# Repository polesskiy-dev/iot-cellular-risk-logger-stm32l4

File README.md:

# IoT Cellular Risk Data Logger
## Based on Cortex M4 STM32L4 and cellular Simcom SIM7070

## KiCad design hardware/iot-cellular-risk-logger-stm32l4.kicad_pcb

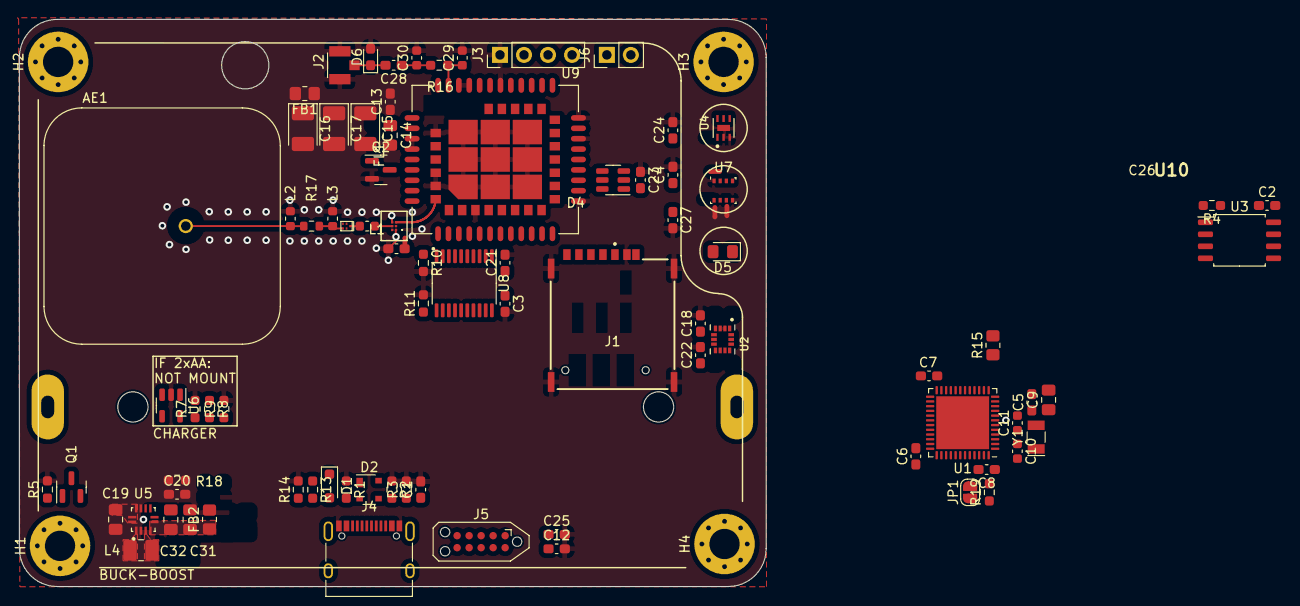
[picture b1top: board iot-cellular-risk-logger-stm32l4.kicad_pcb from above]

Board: 4 copper layers, 79.0 x 60.0 mm, 91 parts (1 on the bottom side), 73 nets.

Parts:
AE1: GNSS Antenna; XDCR_APAE1590R2540AKDB1-T
BT1: 18650 Li-Ion; BAT_BH-18650-PC
C1: 4n7; C_0603_1608Metric_Pad1.08x0.95mm_HandSolder
C2, C3, C4, C5, C6, C7, C8, C12, C13, C18, C21, C22, C23, C24, C25, C26, C27: 100n; C_0603_1608Metric_Pad1.08x0.95mm_HandSolder
C9, C19, C31, C32: 10u; C_0805_2012Metric_Pad1.18x1.45mm_HandSolder
C10, C11: 22p; C_0603_1608Metric
C14: 1u; C_0805_2012Metric_Pad1.18x1.45mm_HandSolder
C15, C16, C17: 100uF; CP_EIA-3528-15_AVX-H_Pad1.50x2.35mm_HandSolder
C20: 1n; C_0603_1608Metric_Pad1.08x0.95mm_HandSolder
C28: 100p; C_0603_1608Metric_Pad1.08x0.95mm_HandSolder
C29, C30: 0p; C_0603_1608Metric
D1: BAT60A; D_SOD-323_HandSoldering
D2: PRTR5V0U2X; SOT-143
D4: SMF05CT1G; SOT-23-6
D5: LED; LED_0805_2012Metric_Pad1.15x1.40mm_HandSolder
D6: TVS 5V; D_0603_1608Metric_Pad1.05x0.95mm_HandSolder
FB1, FB2: 330; R_0805_2012Metric_Pad1.20x1.40mm_HandSolder
FL1: SAFFB1G56KB0F0A; Filter_1109-5_1.1x0.9mm
H1, H2, H3, H4: MountingHole_Pad; MountingHole_3.2mm_M3_Pad_Via
J1: Nano SIM; GCT_SIM8066-6-1-14-01-A_REVA
J2: U.FL Antenna Connector (Male); HRS_U.FL-R-SMT_01_
J3: GSM_USB; PinHeader_1x04_P2.54mm_Vertical
J4: USB Type-C; USB_C_Receptacle_XKB_U262-16XN-4BVC11
J5: TagConnect SWD ARM; Tag-Connect_TC2050-IDC-NL_2x05_P1.27mm_Vertical_with_bottom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
J6: GSM_DEBUG_UART; PinHeader_1x02_P2.54mm_Vertical
JP1: SolderJumper_2_Open; SolderJumper-2_P1.3mm_Open_RoundedPad1.0x1.5mm
L1: 8.2nH; L_0603_1608Metric
L2, L3: 0L; L_0603_1608Metric
L4: 1.5uH; L_1008_2520Metric_Pad1.43x2.20mm_HandSolder
NT1, NT2, NT3, NT6: NetTie_2; NetTie-2_SMD_Pad0.5mm
Q1: IRLML6401; SOT-23
Q2: DTC143Z; SOT-23
R1, R2: 5k1; R_0603_1608Metric_Pad0.98x0.95mm_HandSolder
R3, R18: 1M; R_0603_1608Metric_Pad0.98x0.95mm_HandSolder
R4, R19: 10k; R_0603_1608Metric_Pad0.98x0.95mm_HandSolder
R5, R9, R10, R11, R13, R14: 47k; R_0603_1608Metric_Pad0.98x0.95mm_HandSolder
R7: 2k5; R_0603_1608Metric_Pad0.98x0.95mm_HandSolder
R8: 100k; R_0603_1608Metric_Pad0.98x0.95mm_HandSolder
R15: 1k; R_0805_2012Metric_Pad1.20x1.40mm_HandSolder
R16: 0R; R_0603_1608Metric_Pad0.98x0.95mm_HandSolder
R17: 0R; R_0603_1608Metric
U1: STM32L433CBUx; QFN-48-1EP_7x7mm_P0.5mm_EP5.6x5.6mm
U2: LSM6DSO; PQFN50P250X300X86-14N
U3: W25Q64JV; SOIC-8_5.23x5.23mm_P1.27mm
U4: OPT3001DNPR; SON65P200X200X65-7N
U5: TPS63051; QFN50P250X250X100-12N
U6: MCP73831-2-OT; SOT-23-5
U7: BME280; Bosch_LGA-8_2.5x2.5mm_P0.65mm_ClockwisePinNumbering
U8: TXB0108PWR; TSSOP-20_4.4x6.5mm_P0.65mm
U9: SIM7080G; XCVR_SIM7080G
U10: BGA 524N6 E6327; BGA524N6E6327
Y1: 32.768; Crystal_SMD_EuroQuartz_EQ161-2Pin_3.2x1.5mm

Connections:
+1V8: C21.1, U8.5 (VCCA), U8.6 (OE), U9.40 (VDD_EXT)
+3V3: C2.1, C3.1, C4.1, C5.1, C6.1, C7.1, C8.1, C9.1, C18.1, C22.1, C24.1, C25.1, C26.1, C27.1, FB2.2, J5.1 (VTref), JP1.1 (A), NT1.2, NT2.2, NT3.2, NT6.2, R4.1, R15.1, R18.1, U1.9 (VDDA), U1.24 (VDD), U1.36 (VDDUSB), U1.48 (VDD), U2.5 (VDDIO), U2.8 (VDD), U2.12 (CS), U3.8 (VCC), U8.16 (VCCB)
+5V: D1.1 (K), D2.4 (VCC), R13.1, U6.4 (V_{DD})
+BATT: C19.1, FB1.2, Q1.2 (S), U5.10 (ILIM0), U5.11 (EN), U5.12 (VIN), U6.3 (V_{BAT})
/GSM Module/+GSM_VBAT: C13.1, C14.1, C15.1, C16.1, C17.1, FB1.1, U9.34 (VBAT), U9.35 (VBAT)
/GSM Module/CLK: D4.4 (IO3), J1.C3 (CLK), U9.16 (SIM_CLK)
/GSM Module/CTS: U8.4 (A4), U9.4 (UART1_CTS)
/GSM Module/DATA: D4.5 (IO4), J1.C7 (I/O), U9.15 (SIM_DATA)
/GSM Module/DCD: U8.3 (A3), U9.5 (UART1_DCD)
/GSM Module/DTR: U8.2 (A2), U9.6 (UART1_DTR)
/GSM Module/GNSS_ANT_RF: AE1.1 (A), L2.1, R17.2
/GSM Module/GNSS_M_RF: FL1.4, L3.1, R17.1
/GSM Module/GSM_ANT_RF: C28.2, D6.1 (A1)
/GSM Module/GSM_M_RF: C28.1, C30.1, R16.2
/GSM Module/LNA_RF: L1.1, U10.5 (AI)
/GSM Module/RI: U8.1 (A1), U9.7 (UART1_RI)
/GSM Module/RST: D4.3 (IO2), J1.C2 (RST), U9.17 (SIM_RST)
/GSM Module/RTS: U8.7 (A5), U9.3 (UART1_RTS)
/GSM Module/RX: U8.8 (A6), U9.2 (UART1_RXD)
/GSM Module/SAW_RF: FL1.1, L1.2
/GSM Module/TX: U8.9 (A7), U9.1 (UART1_TXD)
/GSM Module/VCC_LNA: NT6.1, U10.2 (VCC)
/GSM Module/VDD: C23.2, D4.1 (IO1), J1.C1 (VCC), U9.18 (SIM_VDD)
/MCU & Interfaces/+LED: D5.2 (A), R15.2
/MCU & Interfaces/+VBUS: D1.2 (A), J4.A4 (VBUS), J4.A9 (VBUS), J4.B4 (VBUS), J4.B9 (VBUS)
/MCU & Interfaces/BOOT0: JP1.2 (B), R19.2, U1.44 (PH3)
/MCU & Interfaces/GND_SHIELD: C1.1, D2.1 (GND), J4.S1 (SHIELD), R3.1
/MCU & Interfaces/LSE IN: C10.1, U1.3 (PC14), Y1.1
/MCU & Interfaces/LSE OUT: C11.1, U1.4 (PC15), Y1.2
/MCU & Interfaces/QSPI_CLK: U1.13 (PA3), U3.6 (CLK)
/MCU & Interfaces/QSPI_IO0: U1.19 (PB1), U3.5 (DI(IO0))
/MCU & Interfaces/QSPI_IO1: U1.18 (PB0), U3.2 (DO(IO1))
/MCU & Interfaces/QSPI_IO2: U1.17 (PA7), U3.3 (IO2)
/MCU & Interfaces/QSPI_IO3: U1.16 (PA6), U3.7 (IO3)
/MCU & Interfaces/USB_CC1: J4.A5 (CC1), R1.2
/MCU & Interfaces/USB_CC2: J4.B5 (CC2), R2.2
/MCU & Interfaces/_LED: D5.1 (K), U1.2 (PC13)
/MCU & Interfaces/_QSPI_NCS: R4.2, U1.12 (PA2), U3.1 (~CS)
/Power Management Unit (PMU)/+VOUT: C31.1, C32.1, FB2.1, U5.4 (VOUT), U5.5 (FB)
/Power Management Unit (PMU)/IND1: L4.2, U5.1 (L1)
/Power Management Unit (PMU)/IND2: L4.1, U5.3 (L2)
CHARGE_STAT: R5.2, R9.1, U1.40 (PB4)
GND: C1.2, C2.2, C3.2, C4.2, C5.2, C6.2, C7.2, C8.2, C9.2, C10.2, C11.2, C12.2, C13.2, C14.2, C15.2, C16.2, C17.2, C18.2, C19.2, C20.2, C21.2, C22.2, C23.1, C24.2, C25.2, C26.2, C27.2, C29.2, C30.2, C31.2, C32.2, D4.2 (GND), D6.2 (A2), H1.1, H2.1, H3.1, H4.1, J1.C5 (GND), J1.G1 (GND), J1.G2 (GND), J1.G3 (GND), J1.G4 (GND), J2.1 (GND), J2.2 (GND), J3.1, J4.A1 (GND), J4.A12 (GND), J4.B1 (GND), J4.B12 (GND), J5.3 (GND), J5.5 (GND), J5.9 (GNDDetect), L2.2, L3.2, Q2.2 (E), R1.1, R2.1, R3.2, R7.2, R8.2, R9.2, R10.2, R11.2, R14.2, R19.1, U1.8 (VSSA), U1.23 (VSS), U1.35 (VSS), U1.47 (VSS), U1.49 (VSS), U2.1 (SDO/SA0), U2.2 (SDX), U2.3 (SCX), U2.6 (GND), U2.7 (GND), U3.4 (GND), U4.2 (ADDR), U4.3 (GND), U4.7 (EXP), U5.2 (GND), U5.6 (PFM/PWM), U5.9 (GND), U6.2 (V_{SS}), U7.1 (GND), U7.5 (SDO), U7.7 (GND), U8.15 (GND), U9.8 (GND), U9.13 (GND), U9.19 (GND), U9.21 (GND), U9.27 (GND), U9.30 (GND), U9.31 (GND), U9.33 (GND), U9.36 (GND), U9.37 (GND), U9.45 (GND), U9.63 (GND), U9.66 (GND), U9.67 (GND), U9.69 (GND), U9.70 (GND), U9.71 (GND), U9.72 (GND), U9.73 (GND), U9.74 (GND), U9.75 (GND), U9.76 (GND), U9.77 (GND), U10.1 (GND_1), U10.4 (GND_2)
GNSS_EN: U1.11 (PA1), U10.6 (PON)
GNSS_RF: U9.68 (GNSS_ANT), U10.3 (AO)
GSM_EN: Q2.1 (B), U1.10 (PA0)
GSM_RF: C29.1, R16.1, U9.32 (RF_ANT)
IMU_INT1: U1.14 (PA4), U2.4 (INT1)
IMU_INT2: U1.15 (PA5), U2.9 (INT2)
unnamed: J6.1, U9.23 (UART2_RXD)
unnamed: J6.2, U9.22 (UART2_TXD)
unnamed: Q1.1 (G), R8.1
unnamed: Q2.3 (C), U9.39 (PWRKEY)
unnamed: NT3.1, U4.1 (VDD)
unnamed: R18.2, U5.8 (PG)
unnamed: C20.1, U5.7 (SS)
unnamed: R7.1, U6.5 (PROG)
unnamed: R5.1, U6.1 (STAT)
unnamed: NT1.1, U7.2 (CSB), U7.6 (VDDIO)
unnamed: NT2.1, U7.8 (VDD)
unnamed: R10.1, U8.10 (A8)
unnamed: R11.1, U8.11 (B8)
SCL: U1.30 (PA9), U2.13 (SCL), U4.4 (SCL), U7.4 (SCK)
SDA: U1.31 (PA10), U2.14 (SDA), U4.6 (SDA), U7.3 (SDI)
SIM_DETECT: J1.CD, U1.20 (PB2)
SWDCLK: J5.4 (SWCLK/TCK), U1.37 (PA14)
SWDIO: J5.2 (SWDIO/TMS), U1.34 (PA13)
SWO: J5.6 (SWO/TDO), U1.39 (PB3)
USB_N: D2.3 (I/O2), J4.A7 (D-), J4.B7 (D-), U1.32 (PA11)
USB_P: D2.2 (I/O1), J4.A6 (D+), J4.B6 (D+), U1.33 (PA12)
USB_VBUS: R13.2, R14.1, U1.38 (PA15)
_LIGHT_INT: U1.42 (PB6), U4.5 (INT)
_RESET: C12.1, J5.10 (~RESET), U1.7 (NRST)

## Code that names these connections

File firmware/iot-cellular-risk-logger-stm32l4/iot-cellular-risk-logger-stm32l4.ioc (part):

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Mcu.Name=STM32L433C(B-C)Ux
Mcu.Package=UFQFPN48
Mcu.UserName=STM32L433CCUx
PA0.GPIOParameters=GPIO_Label
PA0.GPIO_Label=GSM_EN
PA0.Signal=GPIO_Output
PA1.GPIOParameters=GPIO_Label
PA1.GPIO_Label=GNSS_EN
PA1.Signal=GPIO_Output
PA10.Mode=I2C
PA10.Signal=I2C1_SDA
PA11.Mode=Device
PA11.Signal=USB_DM
PA12.Mode=Device
PA12.Signal=USB_DP
PA13\ (JTMS-SWDIO).Signal=SYS_JTMS-SWDIO
PA14\ (JTCK-SWCLK).Signal=SYS_JTCK-SWCLK
PA2.Mode=Single Bank 1
PA2.Signal=QUADSPI_BK1_NCS
PA3.Mode=Single Bank 1
PA3.Signal=QUADSPI_CLK
PA4.GPIOParameters=GPIO_Label
PA4.GPIO_Label=IMU_INT1
PA4.Signal=GPXTI4
PA5.GPIOParameters=GPIO_Label
PA5.GPIO_Label=IMU_INT2
PA5.Signal=GPXTI5
PA6.Mode=Single Bank 1
PA6.Signal=QUADSPI_BK1_IO3
PA7.Mode=Single Bank 1
PA7.Signal=QUADSPI_BK1_IO2
PA8.GPIOParameters=GPIO_Label
PA8.GPIO_Label=GSM_DCD
PA8.Signal=GPXTI8
PA9.Mode=I2C
PA9.Signal=I2C1_SCL
PB0.Mode=Single Bank 1
PB0.Signal=QUADSPI_BK1_IO1
PB1.Mode=Single Bank 1
PB1.Signal=QUADSPI_BK1_IO0
PB10.Mode=Asynchronous
PB10.Signal=LPUART1_RX
PB11.Mode=Asynchronous
PB11.Signal=LPUART1_TX
PB12.Mode=CTS_RTS
PB12.Signal=LPUART1_RTS
PB13.Mode=CTS_RTS
PB13.Signal=LPUART1_CTS
PB14.GPIOParameters=GPIO_Label
PB14.GPIO_Label=GSM_RI
PB14.Signal=GPXTI14
PB15.GPIOParameters=GPIO_Label
PB15.GPIO_Label=GSM_DTR
PB15.Signal=GPIO_Output
PB2.GPIOParameters=GPIO_Label
PB2.GPIO_Label=SIM_DETECT
PB2.Signal=GPXTI2
PB3\ (JTDO-TRACESWO).Signal=SYS_JTDO-SWO
PB4\ (NJTRST).GPIOParameters=GPIO_Label
PB4\ (NJTRST).GPIO_Label=CHARGE_STAT
PB4\ (NJTRST).Signal=GPIO_Input
PB6.GPIOParameters=GPIO_Label
PB6.GPIO_Label=_LIGHT_INT
PB6.Signal=GPXTI6
PC13.GPIOParameters=GPIO_Label
PC13.GPIO_Label=LED_
PC13.Signal=GPIO_Output
PC14-OSC32_IN\ (PC14).Mode=LSE-External-Oscillator
PC14-OSC32_IN\ (PC14).Signal=RCC_OSC32_IN
PC15-OSC32_OUT\ (PC15).Mode=LSE-External-Oscillator
PC15-OSC32_OUT\ (PC15).Signal=RCC_OSC32_OUT
RCC.HSE_VALUE=8000000
board=custom

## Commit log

2024-01-05 initial commit: add KiCAD empry project
2024-01-05 schematics: add GSM, USART, level shifter, SIM nets&labels
2024-01-05 add firmware CubeMX stm32l433CC6 initial project
2024-01-05 schematics: add most of the elements
2024-01-05 schematics: add QSPI, rework PMU, add sim, gsm, shifter nets
2024-01-17 PCB: manual RF routes done
2024-01-20 Schema: add boot0, reasign IMU INTs
2024-01-21 Schema: split to hierarchical schema
